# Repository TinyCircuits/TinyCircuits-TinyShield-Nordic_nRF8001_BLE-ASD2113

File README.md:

# TinyCircuits TinyShield Nordic nRF8001 Bluetooth LE Board
# ASD2113 Rev3

The design files are located under design_files/ for the TinyCircuits ASD2113 Rev3 PCB.  This is a TinyShield board that has a Nordic Semiconductor nRF8001 Bluetooth Low Energy (or Smart) 4.0 chipset, local power supply and level shifters to connect between the TinyDuino and the Bluetooth LE Module. 

Format is in Cadsoft Eagle format - Eagle version 6.2 was used for the original design.

For more infomation on this, check out the product page at TinyCircuits.com: https://tinycircuits.com/collections/communication/products/bluetooth-low-energy-nordic-tinyshield

# License:

Design by TinyCircuits.
All design files are released under the Creative Commons Attribution Share-Alike 3.0 License, see the following link for details: http://creativecommons.org/licenses/by-sa/3.0

All text above must be included in any redistribution or derived design

This project uses designs and concepts developed as part of the Arduino project and the LilyPad project.  The TinyCircuits design files themselves (schematics, PCB and libraries) are not directly derived from these works' design files and have been created new, however the concepts and basic architecture behind the TinyDuino and TinyLily products are derived and we thank the hard work of the organizations below for their contributions to open-source hardware:
  
Original Arduino Uno Design by Team Arduino

LilyPad Arduino Design by Leah Buechley and Sparkfun Electronics

Please support the open-source hardware community

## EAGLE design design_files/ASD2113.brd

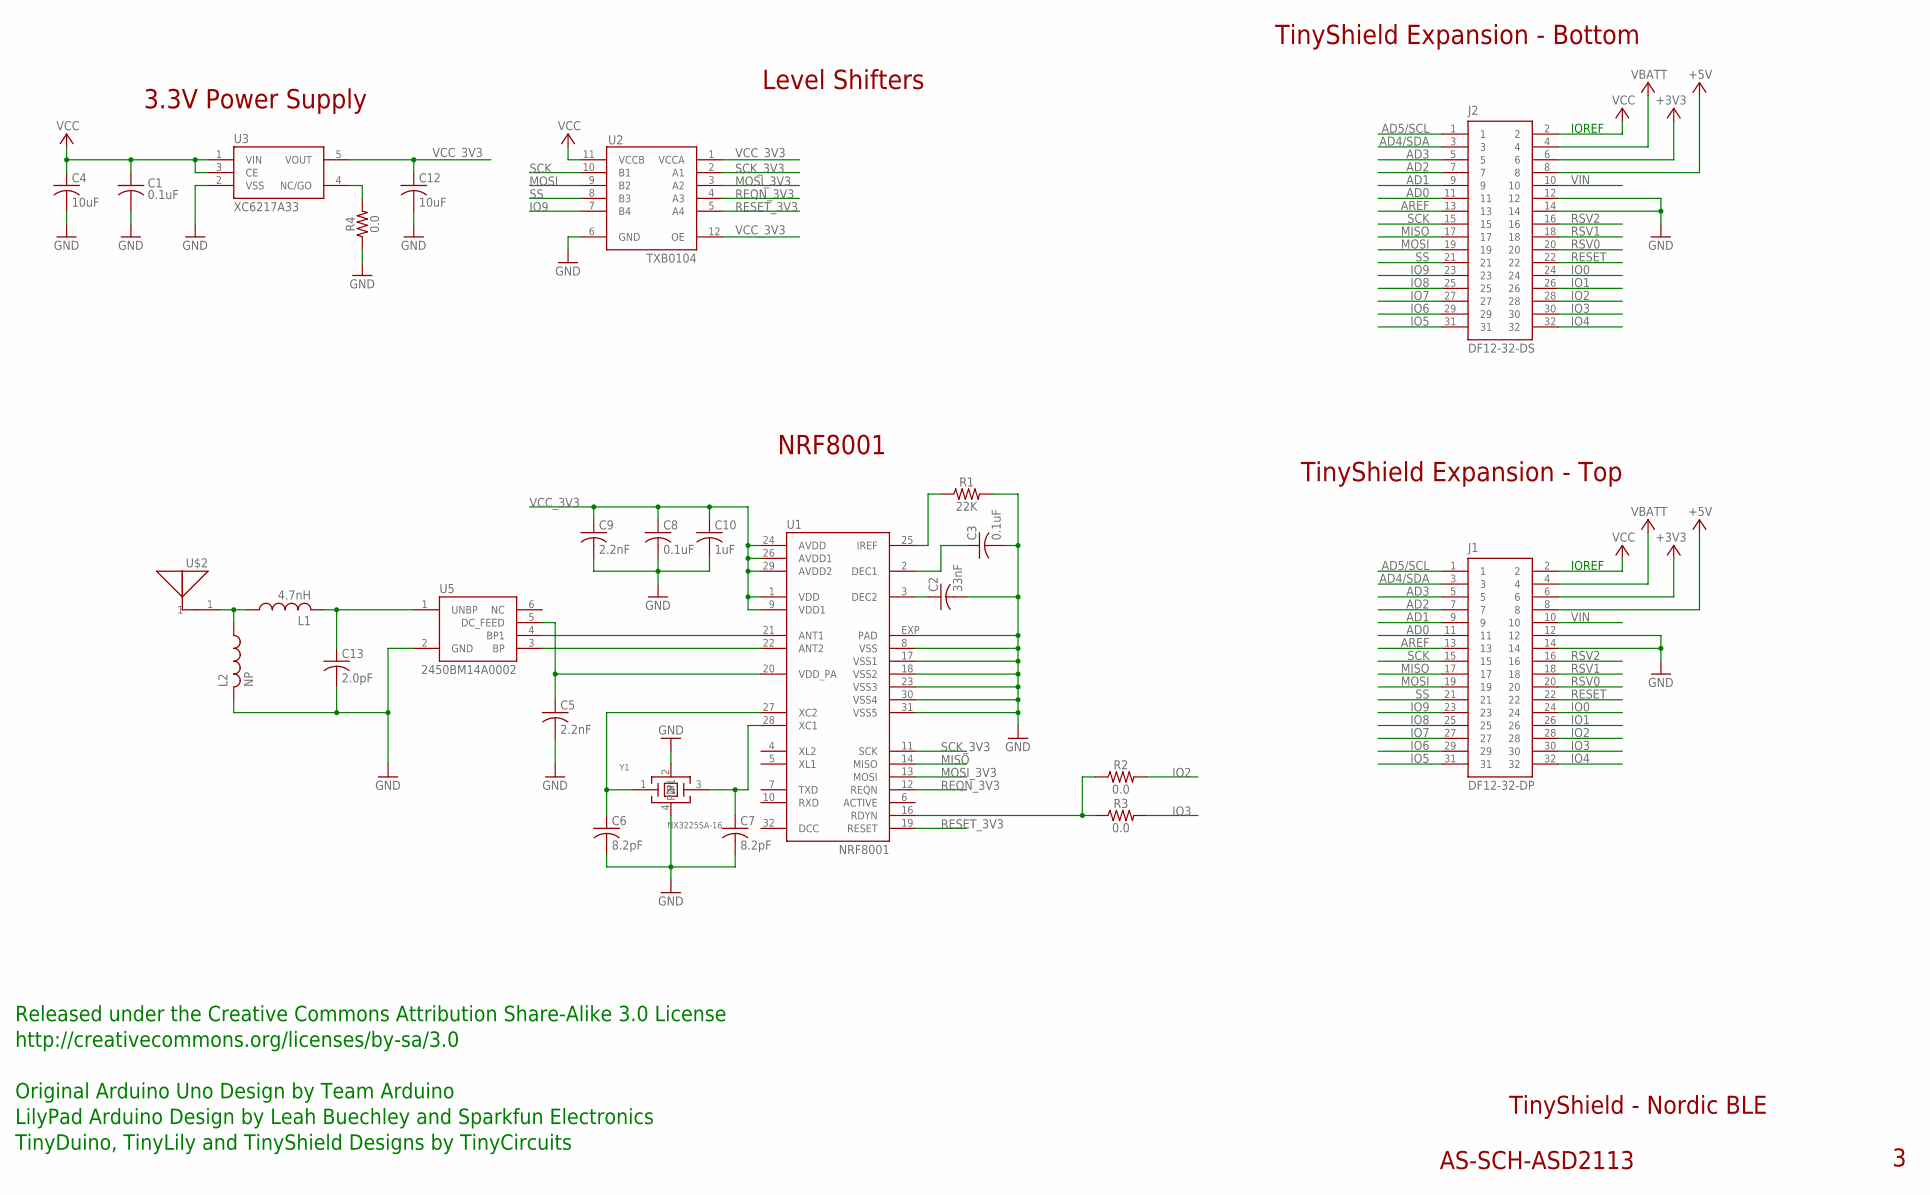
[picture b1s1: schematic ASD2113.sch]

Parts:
C1: 0.1uF; C0402; PARTNO AS-ITM-00008
C2: 33nF; C0402; PARTNO AS-ITM-00248
C3, C8: 0.1uF; C0402
C4, C12: 10uF; C0805; PARTNO AS-ITM-00045
C5, C9: 2.2nF; C0402
C6, C7: 8.2pF; C0402; PARTNO AS-ITM-00247
C10: 1uF; C0402
C13: 2.0pF; C0402; PARTNO AS-ITM-00245
J1: DF12-32-DP; PARTNO AS-ITM-00015
J2: DF12-32-DS; PARTNO AS-ITM-00012
L1: 4.7nH; C0402; PARTNO AS-ITM-00246
L2: NP; C0402
R1: 22K; 0402
R2, R3: 0.0; 0402; PARTNO AS-ITM-00076
R4: 0.0; 0402
U1: NRF8001; ATMEL_QFN32
U2: TXB0104; UQFN-12
U3: XC6217A33; SOT-25; PARTNO AS-ITM-00249
U5: 2450BM14A0002
U$2: AS-ITM-00132; 2450AT18A100; PARTNO AS-ITM-00132
Y1: NX3225SA-16; ABM11; PARTNO AS-ITM-00228

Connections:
+3V3: J1.6, J2.6
+5V: J1.8, J2.8
AD0: J1.11, J2.11
AD1: J1.9, J2.9
AD2: J1.7, J2.7
AD3: J1.5, J2.5
AD4/SDA: J1.3, J2.3
AD5/SCL: J1.1, J2.1
AREF: J1.13, J2.13
GND: C1.2, C2.2, C3.2, C4.2, C5.2, C6.2, C7.2, C8.2, C9.2, C10.2, C12.2, C13.2, J1.12, J1.14, J2.12, J2.14, L2.2, R1.2, R4.1, U1.8 (VSS), U1.17 (VSS1), U1.18 (VSS2), U1.23 (VSS3), U1.30 (VSS4), U1.31 (VSS5), U1.EXP (PAD), U2.6 (GND), U3.2 (VSS), U5.2 (GND), Y1.2, Y1.4 (P1)
IO0: J1.24, J2.24
IO1: J1.26, J2.26
IO2: J1.28, J2.28, R2.2
IO3: J1.30, J2.30, R3.2
IO4: J1.32, J2.32
IO5: J1.31, J2.31
IO6: J1.29, J2.29
IO7: J1.27, J2.27
IO8: J1.25, J2.25
IO9: J1.23, J2.23, U2.7 (B4)
MISO: J1.17, J2.17, U1.14 (MISO)
MOSI: J1.19, J2.19, U2.9 (B2)
MOSI_3V3: U1.13 (MOSI), U2.3 (A2)
unnamed: R1.1, U1.25 (IREF)
unnamed: C6.1, U1.27 (XC2), Y1.1
unnamed: C13.1, L1.2, U5.1 (UNBP)
unnamed: C3.1, U1.2 (DEC1)
unnamed: C2.1, U1.3 (DEC2)
unnamed: U1.22 (ANT2), U5.3 (BP)
unnamed: U1.21 (ANT1), U5.4 (BP1)
unnamed: C5.1, U1.20 (VDD_PA), U5.5 (DC_FEED)
unnamed: C7.1, U1.28 (XC1), Y1.3 (2)
unnamed: L1.1, L2.1, U$2.1
unnamed: R4.2, U3.4 (NC/GO)
RDYN: R2.1, R3.1, U1.16 (RDYN)
REQN_3V3: U1.12 (REQN), U2.4 (A3)
RESET: J1.22, J2.22
RESET_3V3: U1.19 (RESET), U2.5 (A4)
RSV0: J1.20, J2.20
RSV1: J1.18, J2.18
RSV2: J1.16, J2.16
SCK: J1.15, J2.15, U2.10 (B1)
SCK_3V3: U1.11 (SCK), U2.2 (A1)
SS: J1.21, J2.21, U2.8 (B3)
VBATT: J1.4, J2.4
VCC: C1.1, C4.1, J1.2, J2.2, U2.11 (VCCB), U3.1 (VIN), U3.3 (CE)
VCC_3V3: C8.1, C9.1, C10.1, C12.1, U1.1 (VDD), U1.9 (VDD1), U1.24 (AVDD), U1.26 (AVDD1), U1.29 (AVDD2), U2.1 (VCCA), U2.12 (OE), U3.5 (VOUT)
VIN: J1.10, J2.10

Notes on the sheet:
TinyShield Expansion - Bottom
TinyShield - Nordic BLE
AS-SCH-ASD2113
TinyShield Expansion - Top
IOREF
Released under the Creative Commons Attribution Share-Alike 3.0 License
http://creativecommons.org/licenses/by-sa/3.0
LilyPad Arduino Design by Leah Buechley and Sparkfun Electronics
TinyDuino, TinyLily and TinyShield Designs by TinyCircuits
Original Arduino Uno Design by Team Arduino
3.3V Power Supply
NRF8001
Level Shifters

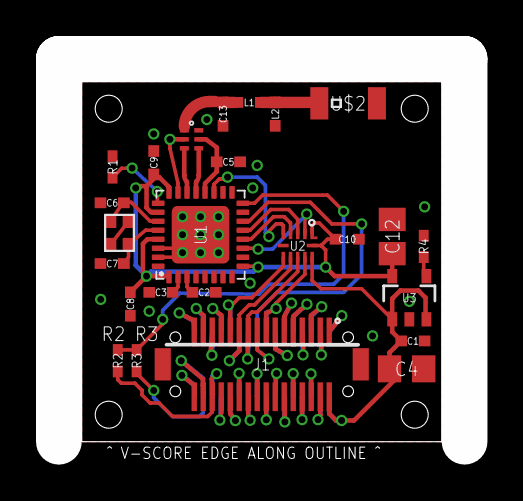
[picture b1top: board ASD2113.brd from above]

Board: 2 copper layers, 20.0 x 20.0 mm, 27 parts (1 on the bottom side), 48 nets.

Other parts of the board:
U$1: DOCFIELD-TINYCIRCUITS-PCB

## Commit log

2015-04-11 :octocat: Added .gitattributes & .gitignore files
2015-06-15 Updated product link
2019-01-02 update format
2019-01-07 updated comments
2019-05-16 added images
2019-05-16 added .zip file
2019-05-20 updated naming
2019-05-21 fix fix fix!
2019-05-21 naming conventions are tough
2019-05-21 Android app
2019-05-21 oops
2019-05-23 updated images
2019-07-22 added .zip
2020-02-11 image update
